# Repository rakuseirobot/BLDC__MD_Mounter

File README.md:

View this project on [CADLAB.io](https://cadlab.io/project/23125). 

# BLDC__MD_Mounter
The mounter for BLDC_MD_DRV10970.

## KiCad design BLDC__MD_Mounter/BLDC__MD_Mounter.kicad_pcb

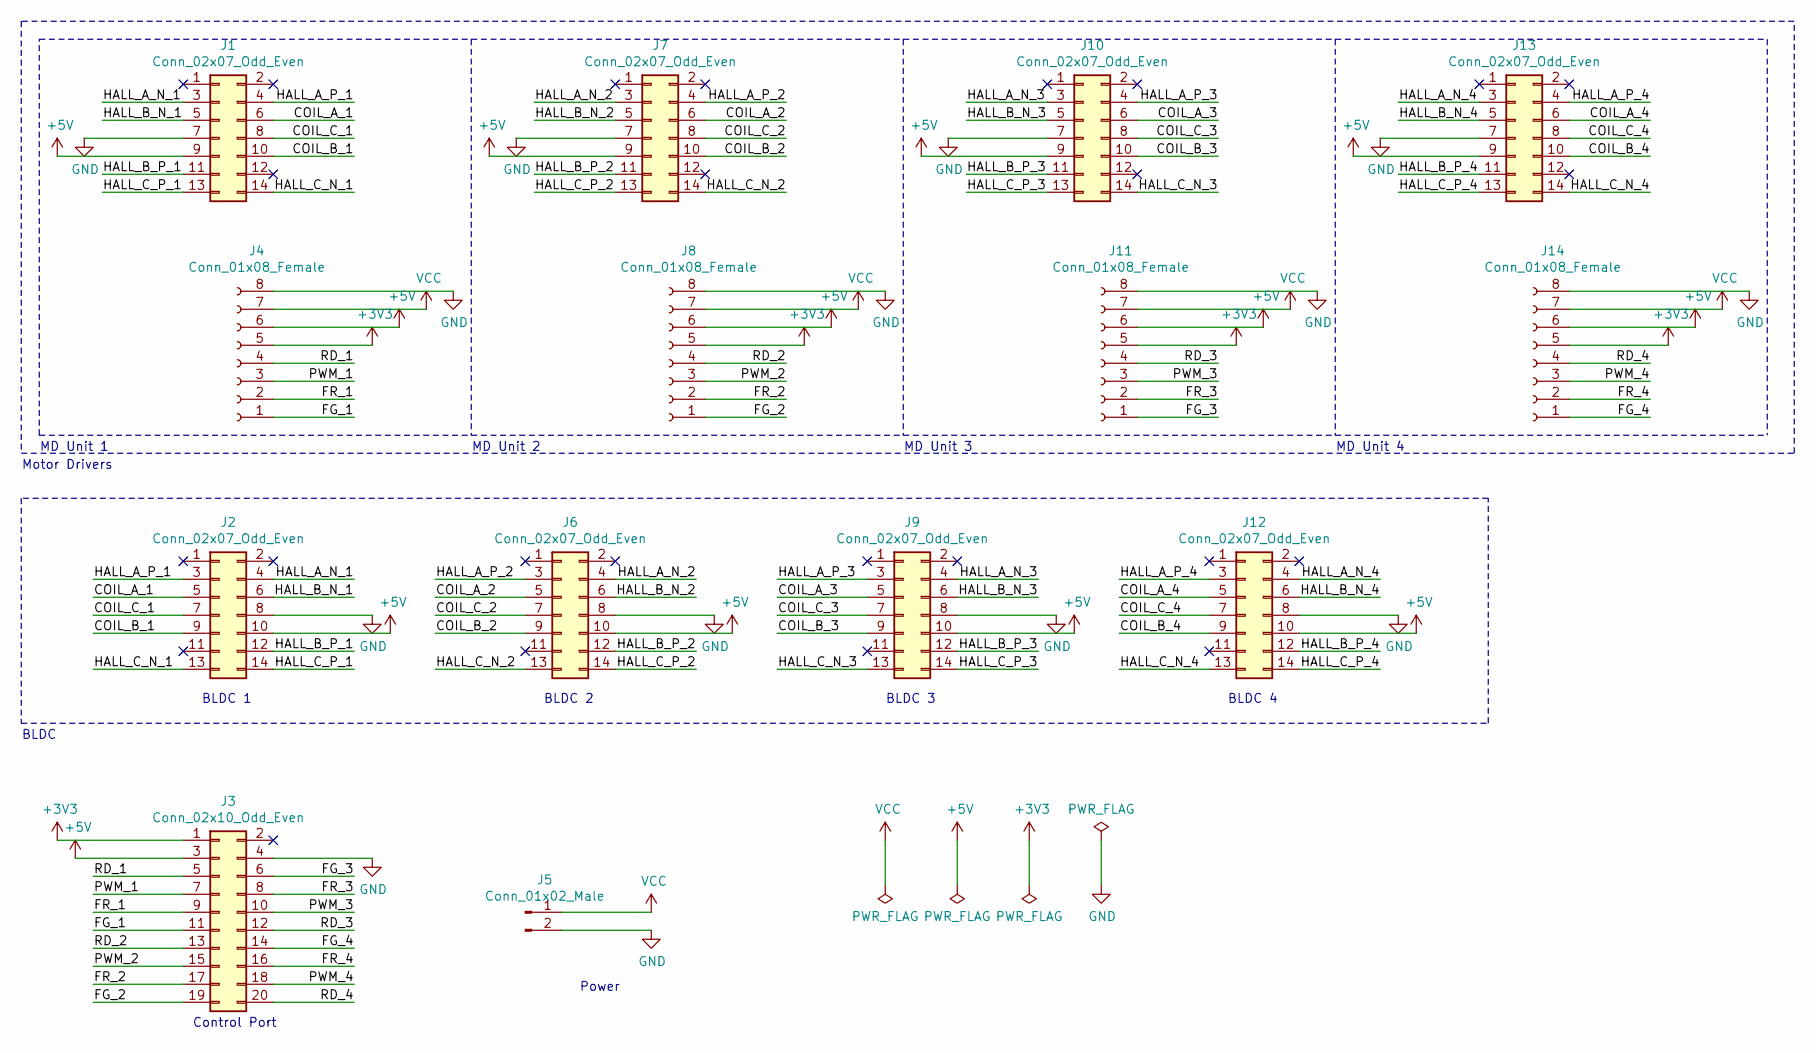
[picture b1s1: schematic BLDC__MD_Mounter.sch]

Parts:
J1, J7, J10, J13: Conn_02x07_Odd_Even; PinSocket_2x07_P2.54mm_Vertical
J2, J6, J9, J12: Conn_02x07_Odd_Even; PinHeader_2x07_P2.54mm_Vertical
J3: Conn_02x10_Odd_Even; PinHeader_2x10_P2.54mm_Vertical
J4, J8, J11, J14: Conn_01x08_Female; PinSocket_1x08_P2.54mm_Vertical
J5: Conn_01x02_Male; JST_VH_B2P-VH_1x02_P3.96mm_Vertical

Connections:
+3V3: J3.1, J4.5, J8.5, J11.5, J14.5
+5V: J1.9, J2.10, J3.3, J4.6, J6.10, J7.9, J8.6, J9.10, J10.9, J11.6, J12.10, J13.9, J14.6
/COIL_A_1: J1.6, J2.5
/COIL_A_2: J6.5, J7.6
/COIL_A_3: J9.5, J10.6
/COIL_A_4: J12.5, J13.6
/COIL_B_1: J1.10, J2.9
/COIL_B_2: J6.9, J7.10
/COIL_B_3: J9.9, J10.10
/COIL_B_4: J12.9, J13.10
/COIL_C_1: J1.8, J2.7
/COIL_C_2: J6.7, J7.8
/COIL_C_3: J9.7, J10.8
/COIL_C_4: J12.7, J13.8
/FG_1: J3.11, J4.1
/FG_2: J3.19, J8.1
/FG_3: J3.6, J11.1
/FG_4: J3.14, J14.1
/FR_1: J3.9, J4.2
/FR_2: J3.17, J8.2
/FR_3: J3.8, J11.2
/FR_4: J3.16, J14.2
/HALL_A_N_1: J1.3, J2.4
/HALL_A_N_2: J6.4, J7.3
/HALL_A_N_3: J9.4, J10.3
/HALL_A_N_4: J12.4, J13.3
/HALL_A_P_1: J1.4, J2.3
/HALL_A_P_2: J6.3, J7.4
/HALL_A_P_3: J9.3, J10.4
/HALL_A_P_4: J12.3, J13.4
/HALL_B_N_1: J1.5, J2.6
/HALL_B_N_2: J6.6, J7.5
/HALL_B_N_3: J9.6, J10.5
/HALL_B_N_4: J12.6, J13.5
/HALL_B_P_1: J1.11, J2.12
/HALL_B_P_2: J6.12, J7.11
/HALL_B_P_3: J9.12, J10.11
/HALL_B_P_4: J12.12, J13.11
/HALL_C_N_1: J1.14, J2.13
/HALL_C_N_2: J6.13, J7.14
/HALL_C_N_3: J9.13, J10.14
/HALL_C_N_4: J12.13, J13.14
/HALL_C_P_1: J1.13, J2.14
/HALL_C_P_2: J6.14, J7.13
/HALL_C_P_3: J9.14, J10.13
/HALL_C_P_4: J12.14, J13.13
/PWM_1: J3.7, J4.3
/PWM_2: J3.15, J8.3
/PWM_3: J3.10, J11.3
/PWM_4: J3.18, J14.3
/RD_1: J3.5, J4.4
/RD_2: J3.13, J8.4
/RD_3: J3.12, J11.4
/RD_4: J3.20, J14.4
GND: J1.7, J2.8, J3.4, J4.8, J5.2, J6.8, J7.7, J8.8, J9.8, J10.7, J11.8, J12.8, J13.7, J14.8
VCC: J4.7, J5.1, J8.7, J11.7, J14.7

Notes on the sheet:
MD Unit 1
MD Unit 2
MD Unit 3
MD Unit 4
BLDC 3
BLDC 4
BLDC
Motor Drivers
Control Port
BLDC 2
BLDC 1
Power

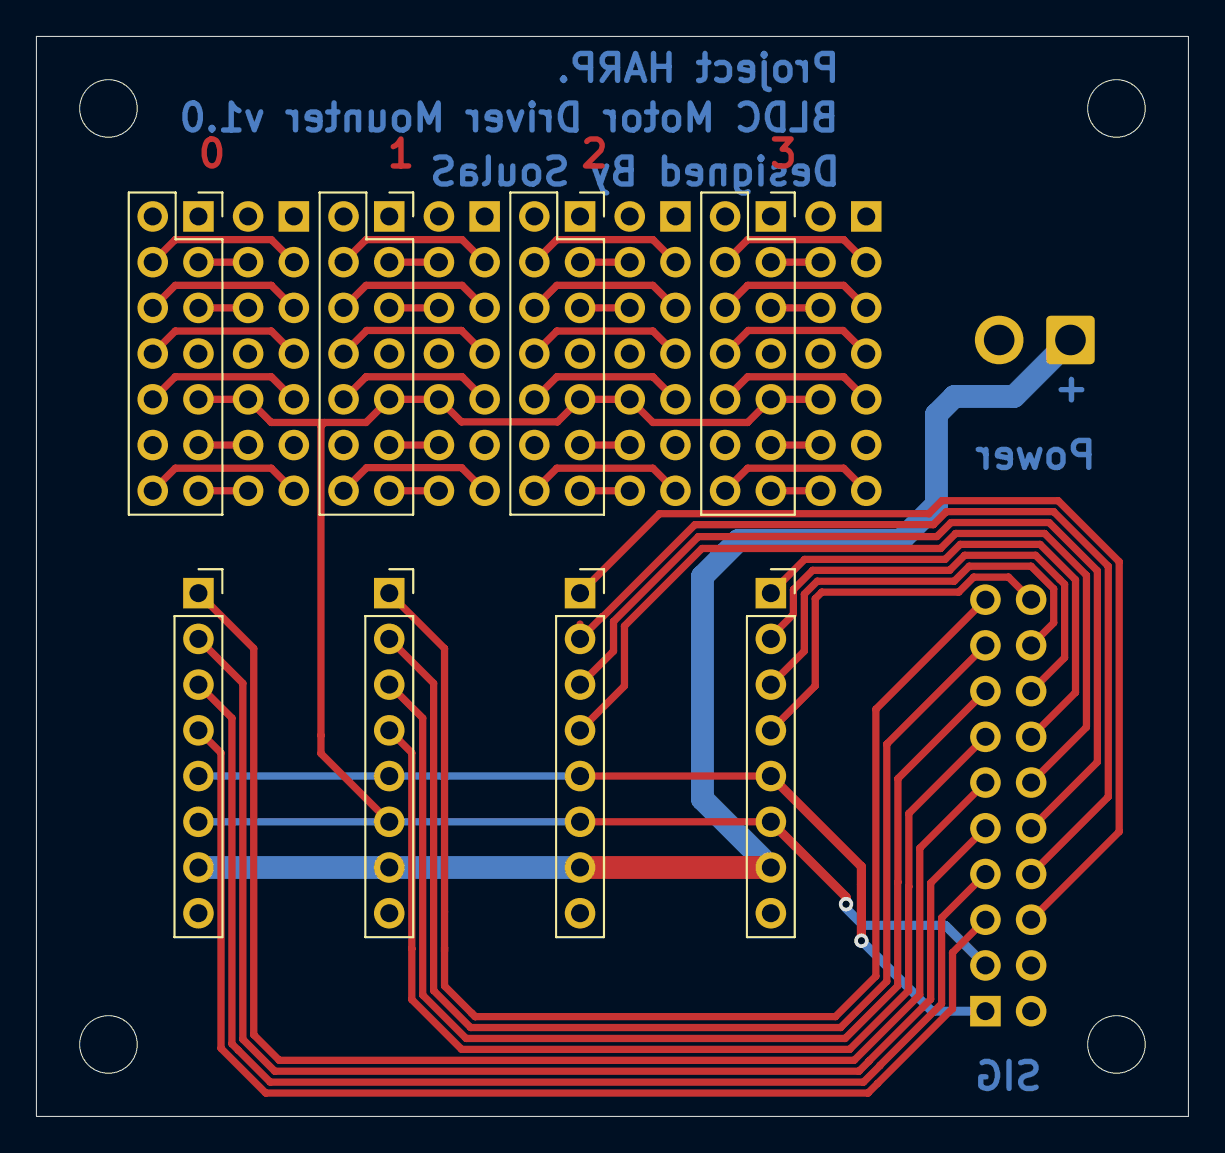
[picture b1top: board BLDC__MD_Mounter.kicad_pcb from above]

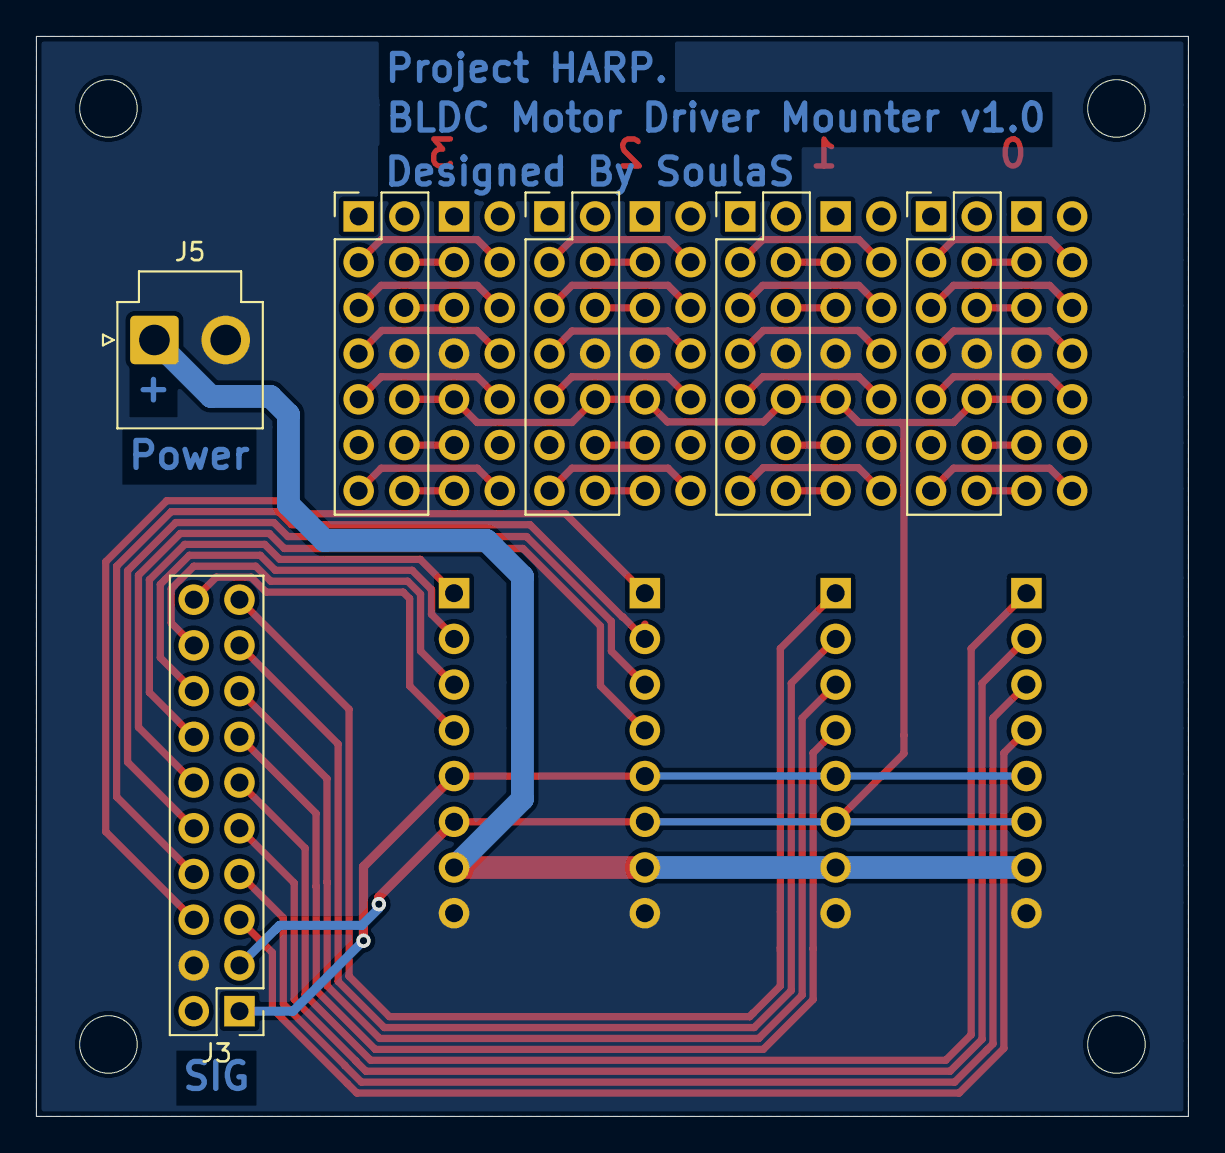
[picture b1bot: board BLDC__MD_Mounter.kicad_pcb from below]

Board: 2 copper layers, 64.0 x 60.0 mm, 14 parts (6 on the bottom side), 56 nets.

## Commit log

2020-07-19 Backlink to CADLAB.io has been added.
2020-07-19 Initialized with KiCad.
2020-07-19 Added some initial datas in schematic
2020-07-19 Placed Connectors on schematic
    for Motor Driver, BLDC, Control and Power.
2020-07-19 Added PWR_FLAGs in schematic
    connected all Power Symbol to the PWR_FLAG.
2020-07-23 Annotated all parts
2020-07-23 Related all symbols and footprints
2020-07-23 Placed all the parts
2020-07-23 Connected some simple lines
2020-07-26 Connected all components. And exported CAD files.
    The CAD file type is .step and there are two pictures of the board, front and back.
2020-07-26 Fixed the location of the single line pinheader bottom side of the board.
2020-08-10 added gerber files for production on elecrow
2020-08-17 Added BOM file
2020-10-29 #fix reverse pin sockets bottom and sig port pin socket.
